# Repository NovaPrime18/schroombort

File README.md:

<div align="center">

# Schroombort

**An over-engineered, battery-powered mechanical soundboard.**

Press a button, hear a dumb sound. Then find out it's also a macro-pad. And a calculator.

[**▶ Watch the cinematic trailer**](https://www.youtube.com/watch?v=MM4cooladaY)

</div>

---

## Renders

<div align="center">
<table>
<tr>
<td align="center" width="50%">
<br>
</td>
<td align="center" width="50%">
<br>
</td>
</tr>
</table>
</div>

---

## What is it..?

Schroombort is a battery-powered soundboard built around **36 mechanical (Cherry MX‑style) switches**, a **Vacuum Fluorescent Display**, and stereo speakers — designed to do way more than it needs to. It runs in one of three configurations, switchable depending on how you're using it.

## ⚙️ Configurations

| Mode | Description |
|------|-------------|
| **Soundboard** | Press a button, and a sound is played straight from the SD card. |
| **Macro-pad** | Plug it into your computer over USB‑C and assign each of the 36 buttons to a custom macro. |
| **Calculator** | Flip it into a fully functional basic calculator. |

## Specs

| Category | Detail |
|---|---|
| **Charging** | Any 5V charger, up to 2A |
| **Power management** | Fully dynamic power-path management — runs entirely on USB, entirely on battery, or a mix of both, seamlessly |
| **Inputs** | 36 configurable mechanical buttons |
| **Audio** | Stereo speakers |
| **Microcontroller** | ATxmega256A3U |
| **Display** | Vacuum Fluorescent Display (VFD) |
| **Connectivity** | USB-C |

## Repository structure

```
schroombort/
├── HardwareSchroombortFirmware/   # Firmware source code
├── PCB Files/                     # KiCad hardware design files
├── Pictures/                      # Renders & photos of the build
└── LICENSE                        # CERN-OHL-S v2.0
```

## Cinematic trailer

Because a README alone can't do it justice:

**[▶ https://www.youtube.com/watch?v=MM4cooladaY](https://www.youtube.com/watch?v=MM4cooladaY)**

## License

This project is open hardware, licensed under the **[CERN Open Hardware Licence Version 2 - Strongly Reciprocal (CERN-OHL-S v2.0)](https://ohwr.org/cern_ohl_s_v2.txt)**.

Any modified versions of the hardware distributed must remain under the same license, and source (including any modifications) must be made available.

---

<div align="center">
<sub>Built with too much love for a device whose main job is playing dumb sounds.</sub>
</div>

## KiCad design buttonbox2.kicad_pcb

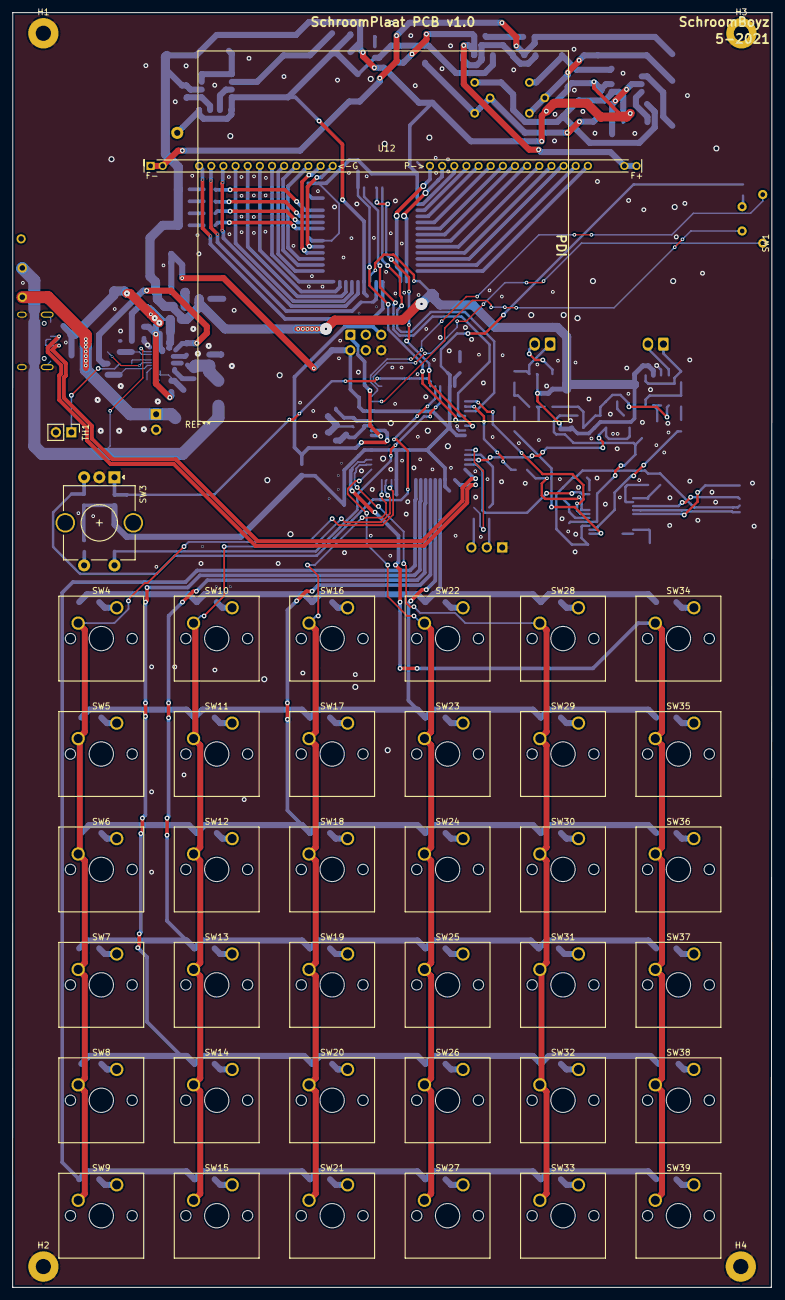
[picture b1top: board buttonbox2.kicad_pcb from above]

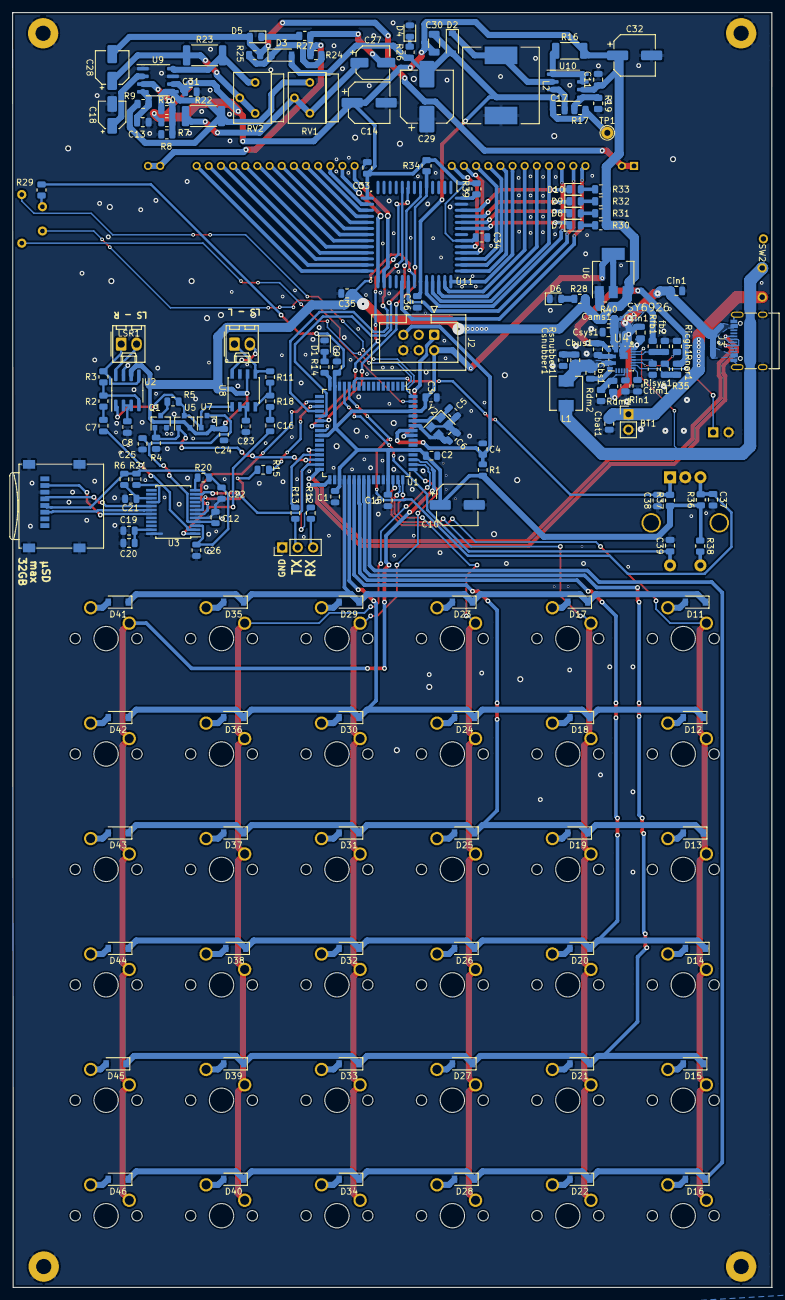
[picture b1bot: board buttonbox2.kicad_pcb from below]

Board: 2 copper layers, 125.0 x 209.8 mm, 213 parts (169 on the bottom side), 172 nets.

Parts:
BT1: Battery; PinHeader_1x02_P2.54mm_Vertical
C1, C2, C3, C4, C9, C11, C13, C19, C24, C25, C26, C31, C33, C34, C35, C36, C37, C38, C39: 100n; C_0805_2012Metric
C5, C6: 10p; C_0805_2012Metric
C7, C16, C20, C22: 10u; C_0805_2012Metric
C8, C12, C21, C23: 1u; C_0805_2012Metric
C10, C14, C32: 100u; CP_Elec_6.3x5.4
C15: 4.7u; C_0805_2012Metric
C17: 1n; C_0805_2012Metric
C18: 1u; CP_Elec_4x5.4
C27, C28: 10u-50V; CP_Elec_5x5.4
C29: 100u-50V; CP_Elec_8x10.5
C30: 10u 50V; C_1206_3216Metric
Cams1: C; C_0805_2012Metric
Cbat1: 20uF; C_0805_2012Metric
Cbs1: 1nF; C_0805_2012Metric
Cbus1: 20uF; C_0805_2012Metric
Cin1: 20uF; C_0805_2012Metric
Csin1: 100nF; C_0805_2012Metric
Csnubber1: DNP; C_0805_2012Metric
Csys1: 20uF; C_0805_2012Metric
Ctim1: 100nF; C_0805_2012Metric
D1, D4, D5, D6, D7, D8, D9, D10: LED; LED_0805_2012Metric
D2: 1N5819; D_SOD-123
D3: 3.6V; D_SOD-123
D11, D12, D13, D14, D15, D16, D17, D18, D19, D20, D21, D22, D23, D24, D25, D26, D27, D28, D29, D30, D31, D32, D33, D34, D35, D36, D37, D38, D39, D40, D41, D42, D43, D44, D45, D46: D_Small; D_SOD-123
H1, H2, H3, H4: MountingHole_Pad; MountingHole_2.5mm_Pad
J2: AVR-PDI-6; IDC-Header_2x03_P2.54mm_Vertical
J3: USB_C_Receptacle_USB2.0; USB_C_Receptacle_XKB_U262-16XN-4BVC11
J4: Conn_01x03_Male; PinHeader_1x03_P2.54mm_Vertical
J6: Micro_SD_Card; microSD_HC_Wuerth_693072010801
L1: 2.2uH; L_Sunlord_MWSA0518_5.4x5.2mm
L2: 470u; L_12x12mm_H8mm
LSL1: Speaker; Molex_KK-254_AE-6410-02A_1x02_P2.54mm_Vertical
LSR1: Speaker; Molex_KK-254_AE-6410-02A_1x02_P2.54mm_Vertical
Q1: 2N7002; SOT-23
R1, R2, R4, R5, R7, R8, R10, R14, R18, R27, R28, R29, R34, R36, R37, R38: 10K; R_0805_2012Metric
R3, R11: TBD; R_0805_2012Metric
R6, R20, R21: 22K; R_0805_2012Metric
R9: 2.2K; R_0805_2012Metric
R12, R13: 100R; R_0805_2012Metric
R15: 1K; R_0805_2012Metric
R16: 0.3 2W; R_2010_5025Metric
R17: 20K; R_0805_2012Metric
R19: 390K; R_0805_2012Metric
R22, R23: 150 2W; R_2512_6332Metric
R24, R25: 100; R_0805_2012Metric
R26: 100K; R_0805_2012Metric
R30, R31, R32, R33: 330; R_0805_2012Metric
R35: 4.4K; R_0805_2012Metric
R39: 56K; R_0805_2012Metric
R40: DNP; R_0805_2012Metric
RV1, RV2: 500; Potentiometer_Bourns_3339S_Horizontal
Rdm1: 33K; R_0805_2012Metric
Rdm2: 9.1K; R_0805_2012Metric
Rfb1: 33K; R_0805_2012Metric
Ricgh1: 10.666K; R_0805_2012Metric
Rin1: 1K; R_0805_2012Metric
Risys1: 36K; R_0805_2012Metric
Rnor1: 22K; R_0805_2012Metric
Rsnubber1: DNP; R_0805_2012Metric
SW1: SW_SP3T; schakelaar
SW2: SW_SPDT; SWINTCHFORBATTERY
SW3: Rotary_Encoder_Switch; RotaryEncoder_Alps_EC11E-Switch_Vertical_H20mm_CircularMoun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
SW4, SW5, SW6, SW7, SW8, SW9, SW10, SW11, SW12, SW13, SW14, SW15, SW16, SW17, SW18, SW19, SW20, SW21, SW22, SW23, SW24, SW25, SW26, SW27, SW28, SW29, SW30, SW31, SW32, SW33, SW34, SW35, SW36, SW37, SW38, SW39: SW_Push; SW_Cherry_MX_1.00u_PCB_BETTER
TH1: Thermistor_NTC; PinHeader_1x02_P2.54mm_Vertical
TP1: TestPoint; TestPoint_THTPad_D2.0mm_Drill1.0mm
U1: ATxmega256A3-AU; TQFP-64_14x14mm_P0.8mm
U2, U8, U9: LM4871; SOIC-8_3.9x4.9mm_P1.27mm
U3: YX5200-24SS; SSOP-24_5.3x8.2mm_P0.65mm
U4: SY6926; QFN-20_L4.0-W4.0-P0.45-BL
U5, U7: DMG3415; SOT-23
U6: AMS1117-3.3; SOT-223-3_TabPin2
U10: MC34063AD; SOIC-8_3.9x4.9mm_P1.27mm
U11: PT6311; LQFP-52_14x14_Pitch1mm
U12: VFD_HNV-12SS62; VFD_12SGMT
Y2: Crystal_GND24; Crystal_SMD_3225-4Pin_3.2x2.5mm
fb2: 10.3K; R_0805_2012Metric

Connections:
+3V3: C1.1, C2.1, C3.1, C9.1, C10.1, C15.1, J2.2, R1.1, R29.1, R36.1, R37.1, R38.1, U1.15, U1.25, U1.35, U1.45, U1.53, U1.61, U6.2
+5P: C12.1, C25.1, U3.4, U7.3
/MP3_player/3V3OUT: C22.1, C26.1, J6.4, R6.1, R20.2, R21.1, U3.3
/MP3_player/AMP_SHDN: R5.1, U2.1, U5.3, U7.1, U8.1
/MP3_player/DACL: C16.2, U3.1
/MP3_player/DACR: C7.2, U3.2
/MP3_player/SD_CLK: J6.5, U3.17
/MP3_player/SD_CMD: J6.3, U3.18
/MP3_player/SD_DAT: J6.7, U3.19
/MP3_player/VCOM: C19.1, C20.1, U3.23
BAT: L1.2, SW2.2, U4.19
BST: Cbs1.1, U4.7
BUS: Cbus1.1, Rnor1.1, U4.4
BUSY: U1.31, U3.11
CLK: U1.23, U11.8
Column1: SW4.2, SW5.2, SW6.2, SW7.2, SW8.2, SW9.2, U1.46
Column2: SW10.2, SW11.2, SW12.2, SW13.2, SW14.2, SW15.2, U1.47
Column3: SW16.2, SW17.2, SW18.2, SW19.2, SW20.2, SW21.2, U1.48
Column4: SW22.2, SW23.2, SW24.2, SW25.2, SW26.2, SW27.2, U1.49
Column5: SW28.2, SW29.2, SW30.2, SW31.2, SW32.2, SW33.2, U1.50
Column6: SW34.2, SW35.2, SW36.2, SW37.2, SW38.2, SW39.2, U1.51
D+: J3.A6, J3.B6, U1.33
D-: J3.A7, J3.B7, U1.32
DIN: U1.21, U11.6
DOUT: R34.2, U1.22, U11.5
FIL+: C27.2, R24.1, R27.1, U12.40, U12.41
FIL-: C28.2, D5.2, R25.2, U12.1, U12.2
HW_RX: R12.1, U1.28
HW_TX: R13.1, U1.29
LX: Cbs1.2, L1.1, Rsnubber1.2, U4.6
unnamed: BT1.1, Cbat1.1, SW2.3
unnamed: C5.2, U1.59, Y2.1
unnamed: C6.1, U1.58, Y2.3
unnamed: C7.1, R2.2
unnamed: C8.1, U2.2, U2.3
unnamed: C13.1, R9.2, U9.4
unnamed: C16.1, R18.2
unnamed: C17.1, U10.3
unnamed: C18.1, U9.2
unnamed: C21.1, R6.2, U3.15
unnamed: C23.1, U8.2, U8.3
unnamed: C27.1, R22.1, RV1.2, RV1.3
unnamed: C28.1, R23.1, RV2.2, RV2.3
unnamed: C37.1, R36.2, SW3.B, U1.12
unnamed: C38.2, R37.2, SW3.A, U1.11
unnamed: C39.1, SW3.S2, U1.13
unnamed: Csnubber1.1, Rsnubber1.1
unnamed: Csys1.1, R40.2, Rfb1.2, U4.3
unnamed: Ctim1.1, U4.13
unnamed: D1.2, R14.2
unnamed: D2.1, L2.1, U10.2
unnamed: D3.1, R24.2, R25.1
unnamed: D4.1, R26.2
unnamed: D5.1, R27.2
unnamed: D6.2, R28.2
unnamed: D7.1, U11.47
unnamed: D7.2, R30.2
unnamed: D8.1, U11.48
unnamed: D8.2, R31.2
unnamed: D9.1, U11.49
unnamed: D9.2, R32.2
unnamed: D10.1, U11.50
unnamed: D10.2, R33.2
unnamed: D11.2, SW4.1
unnamed: D12.2, SW5.1
unnamed: D13.2, SW6.1
unnamed: D14.2, SW7.1
unnamed: D15.2, SW8.1
unnamed: D16.2, SW9.1
unnamed: D17.2, SW10.1
unnamed: D18.2, SW11.1
unnamed: D19.2, SW12.1
unnamed: D20.2, SW13.1
unnamed: D21.2, SW14.1
unnamed: D22.2, SW15.1
unnamed: D23.2, SW16.1
unnamed: D24.2, SW17.1
unnamed: D25.2, SW18.1
unnamed: D26.2, SW19.1
unnamed: D27.2, SW20.1
unnamed: D28.2, SW21.1
unnamed: D29.2, SW22.1
unnamed: D30.2, SW23.1
unnamed: D31.2, SW24.1
unnamed: D32.2, SW25.1
unnamed: D33.2, SW26.1
unnamed: D34.2, SW27.1
unnamed: D35.2, SW28.1
unnamed: D36.2, SW29.1
unnamed: D37.2, SW30.1
unnamed: D38.2, SW31.1
unnamed: D39.2, SW32.1
unnamed: D40.2, SW33.1
unnamed: D41.2, SW34.1
unnamed: D42.2, SW35.1
unnamed: D43.2, SW36.1
unnamed: D44.2, SW37.1
unnamed: D45.2, SW38.1
unnamed: D46.2, SW39.1
unnamed: J2.1, U1.56
unnamed: J4.2, R13.2
unnamed: J4.3, R12.2
unnamed: LSL1.1, R11.1, U8.5
unnamed: LSL1.2, U8.8
unnamed: LSR1.1, R3.1, U2.5
unnamed: LSR1.2, U2.8
unnamed: Q1.3, R5.2
unnamed: R2.1, R3.2, U2.4
unnamed: R9.1, R10.1, R22.2, RV1.1, U9.5
unnamed: R7.2, R8.1, R10.2, U9.3
unnamed: R11.2, R18.1, U8.4
unnamed: R15.1, U3.7
unnamed: R16.1, U10.1, U10.7, U10.8
unnamed: R17.1, R19.1, U10.5
unnamed: R20.1, U3.12
unnamed: R21.2, U3.16
unnamed: R23.2, RV2.1, U9.8
unnamed: R29.2, SW1.3
unnamed: R35.1, Rnor1.2, U4.14
unnamed: R35.2, TH1.1
unnamed: R38.2, SW3.S1
unnamed: R39.2, U11.52
unnamed: Rdm1.1, Rdm2.1, U4.11
unnamed: Rfb1.1, U4.18, fb2.2
unnamed: Ricgh1.1, U4.15
unnamed: Rin1.1, U4.12
unnamed: Risys1.2, U4.16
unnamed: SW1.1, U1.1
unnamed: SW1.2, U1.64
unnamed: SW1.4, U1.63
unnamed: U11.15, U12.26
unnamed: U11.16, U12.27
unnamed: U11.17, U12.28
unnamed: U11.18, U12.29
unnamed: U11.19, U12.30
unnamed: U11.20, U12.31
unnamed: U11.21, U12.32
unnamed: U11.22, U12.33
unnamed: U11.23, U12.34
unnamed: U11.24, U12.35
unnamed: U11.25, U12.36
unnamed: U11.26, U12.37
unnamed: U11.27, U12.25
unnamed: U11.28, U12.24
unnamed: U11.31, U12.5
unnamed: U11.32, U12.6
unnamed: U11.35, U12.7
unnamed: U11.36, U12.8
unnamed: U11.37, U12.9
unnamed: U11.38, U12.10
unnamed: U11.39, U12.11
unnamed: U11.40, U12.12
unnamed: U11.41, U12.13
unnamed: U11.42, U12.14
unnamed: U11.43, U12.15
unnamed: U11.44, U12.16
PGNDBAT: BT1.2, C1.2, C2.2, C3.2, C4.2, C5.1, C6.2, C8.2, C9.2, C10.2, C11.2, C12.2, C13.2, C14.2, C15.2, C18.2, C19.2, C20.2, C21.2, C22.2, C23.2, C24.2, C25.2, C26.2, C29.1, C31.2, C32.2, C33.2, C34.2, C35.2, C36.1, C37.2, C38.1, C39.2, Cams1.2, Cbat1.2, Cbus1.2, Cin1.2, Csin1.2, Csnubber1.2, Csys1.2, Ctim1.2, D1.1, D4.2, D6.1, H1.1, H2.1, H3.1, H4.1, J2.6, J3.A1, J3.A12, J3.B1, J3.B12, J3.S1, J4.1, J6.6, J6.9, L2.2, Q1.2, R4.2, R8.2, R19.2, Rdm2.2, Ricgh1.2, Rin1.2, Risys1.1, SW3.C, TH1.2, U1.14, U1.24, U1.34, U1.44, U1.52, U1.60, U2.7, U3.5, U3.24, U4.5, U4.20, U6.1, U8.7, U9.1, U9.7, U11.51, Y2.2, Y2.4, fb2.1
PLAYER_ON: Q1.1, R4.1, U1.30, U5.1
RESET: C4.1, J2.5, R1.2, U1.57
RX: U1.18, U3.6
Row1: D11.1, D17.1, D23.1, D29.1, D35.1, D41.1, U1.36
Row2: D12.1, D18.1, D24.1, D30.1, D36.1, D42.1, U1.37
Row3: D13.1, D19.1, D25.1, D31.1, D37.1, D43.1, U1.38
Row4: D14.1, D20.1, D26.1, D32.1, D38.1, D44.1, U1.39
Row5: D15.1, D21.1, D27.1, D33.1, D39.1, D45.1, U1.40
Row6: D16.1, D22.1, D28.1, D34.1, D40.1, D46.1, U1.41
SIN: Cin1.1, Csin1.1, J3.A4, J3.A9, J3.B4, J3.B9, Rdm1.2, U4.1, U4.2
STATLED: R14.1, U1.16
STB: U1.20, U11.9
SYS: C11.1, C14.1, C24.1, C30.1, C31.1, C32.1, C33.1, C34.1, C35.1, Cams1.1, R7.1, R16.2, R28.1, R30.1, R31.1, R32.1, R33.1, R34.1, R39.1, R40.1, U2.6, U5.2, U6.3, U7.2, U8.6, U9.6, U10.6, U11.14, U11.33, U11.45
TX: R15.2, U1.19
VEE: C17.2, C29.2, C30.2, C36.2, D2.2, D3.2, R17.2, R26.1, TP1.1, U10.4, U11.34

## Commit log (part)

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2021-05-15 asdiufhyljk
2021-05-15 Added hardware battery disconnect
2021-05-15 Ja crap toch weer aan de PCB gezeten
2021-05-17 Changed oscillator capacitor values from 22pF to 10pF
2021-05-18 Added SY6926 component values and some minor cleanup
2021-05-18 Slight footprint shuffle for the VFD
2021-05-18 alles op B.cu ivm assemblage
2021-05-18 Added footprint of U9
2021-05-18 shuffled things around
2021-05-24 NTC circuit and values added
2021-06-03 Added a rotary encoder and almost all BC values
2021-06-11 Final schematic edits, PCB layout
2021-06-11 pretty much routed everything
2021-06-18 Fixed some DRC errors and some incorrect wiring
2021-06-18 Added SYS disconnect, routed USB, changed few things
2021-06-19 Shrank the PCB size, rerouted stuff, added a lot of silkscreen art.
2021-06-20 Changed a lot, ordered the final thing
2021-07-01 Added SchroombortFirmware folder
2022-01-15 Set theme jekyll-theme-cayman
2022-01-15 Set theme jekyll-theme-hacker
